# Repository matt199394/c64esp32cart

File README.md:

Inspired on  chat64 cart by Bart Venneker and Theo van den Beld (https://github.com/bvenneker/Chat64), same hardware with some midifications:
- SD card
- 27C512 EEPROM
- add jumpers to select 8k memory inside EEPROM
- add transistor to control EXROM line
- standart or ultiMax mode jumper
  
 About the code:
  The arduino skeck and ACME assembly code are a working progress, there are many bugs to fix, expecialy SD directory code.
  Not all SIDs file are playable, same as PRG file.
  
Feaures:
- Run PRG file
- play SID files and show SID info
- show koala images
- show current time
- show current weather
- show news by using 2x2 charset

  Video to show the cart in action: https://www.youtube.com/watch?v=Q0KYe2STK2w
  
Any help is appreciate,
Have fun!

Matteo

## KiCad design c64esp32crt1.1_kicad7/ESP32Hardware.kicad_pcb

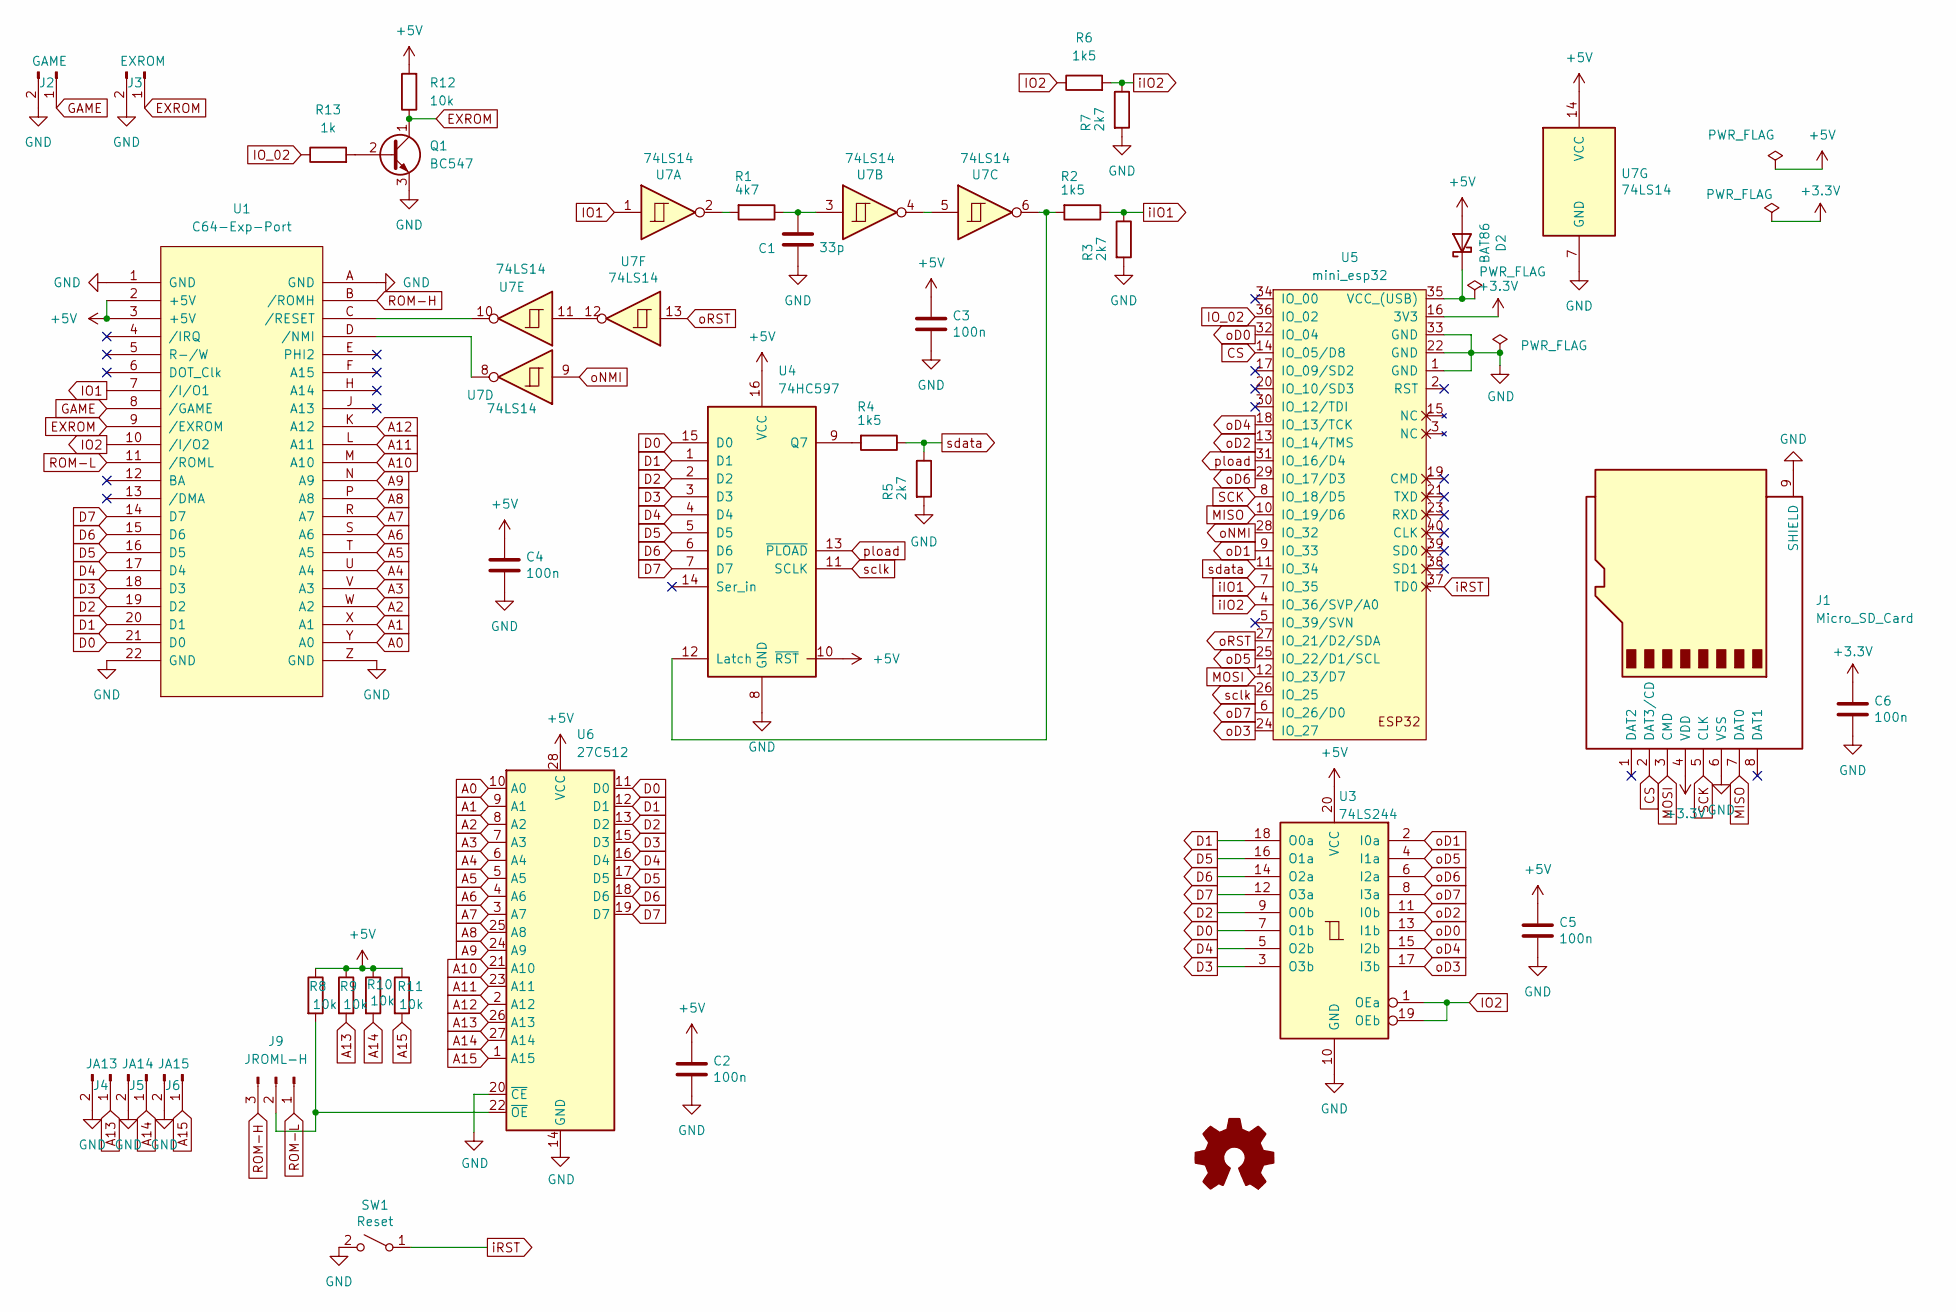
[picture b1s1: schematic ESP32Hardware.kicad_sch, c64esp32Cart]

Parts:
C1: 33p; C_Disc_D3.0mm_W1.6mm_P2.50mm
C2, C3, C4, C5, C6: 100n; C_0805_2012Metric
D2: BAT86; D_DO-34_SOD68_P7.62mm_Horizontal
J1: Micro_SD_Card; J_SD_Card-micro_socket_A
J2: GAME; PinHeader_1x02_P2.54mm_Vertical
J3: EXROM; PinHeader_1x02_P2.54mm_Vertical
J4: JA13; PinHeader_1x02_P2.54mm_Vertical
J5: JA14; PinHeader_1x02_P2.54mm_Vertical
J6: JA15; PinHeader_1x02_P2.54mm_Vertical
J9: JROML-H; PinHeader_1x03_P2.54mm_Vertical
LOGO1: Logo_Open_Hardware_Small; OSHW-Logo2_14.6x12mm_SilkScreen
Q1: BC547; TO-92_Inline
R1: 4k7; R_0805_2012Metric
R2, R4, R6: 1k5; R_0805_2012Metric
R3, R5, R7: 2k7; R_0805_2012Metric
R8, R9, R10, R11, R12: 10k; R_0805_2012Metric
R13: 1k; R_0805_2012Metric
SW1: Reset; SW_Tactile_SKHH_Angled
U1: C64-Exp-Port; C64-Cart-NoSilkS
U3: 74LS244; SOIC-20W_7.5x12.8mm_P1.27mm
U4: 74HC597; SOIC-16W_5.3x10.2mm_P1.27mm
U5: mini_esp32; ESP32_mini
U6: 27C512; DIP-28_W15.24mm
U7: 74LS14; SOIC-14_3.9x8.7mm_P1.27mm

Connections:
+3.3V: C6.1, J1.4 (VDD), U5.16 (3V3)
+5V: C2.1, C3.1, C4.1, C5.1, D2.2 (A), R8.1, R9.1, R10.1, R11.1, R12.2, U1.2 (+5V), U1.3 (+5V), U3.20 (VCC), U4.10 (~RST), U4.16 (VCC), U6.28 (VCC), U7.14 (VCC)
A0: U1.Y (A0), U6.10 (A0)
A1: U1.X (A1), U6.9 (A1)
A2: U1.W (A2), U6.8 (A2)
A3: U1.V (A3), U6.7 (A3)
A4: U1.U (A4), U6.6 (A4)
A5: U1.T (A5), U6.5 (A5)
A6: U1.S (A6), U6.4 (A6)
A7: U1.R (A7), U6.3 (A7)
A8: U1.P (A8), U6.25 (A8)
A9: U1.N (A9), U6.24 (A9)
A10: U1.M (A10), U6.21 (A10)
A11: U1.L (A11), U6.23 (A11)
A12: U1.K (A12), U6.2 (A12)
A13: J4.1, R9.2, U6.26 (A13)
A14: J5.1, R10.2, U6.27 (A14)
A15: J6.1, R11.2, U6.1 (A15)
CS: J1.2 (DAT3/CD), U5.14 (IO_05/D8)
D0: U1.21 (D0), U3.7 (O1b), U4.15 (D0), U6.11 (D0)
D1: U1.20 (D1), U3.18 (O0a), U4.1 (D1), U6.12 (D1)
D2: U1.19 (D2), U3.9 (O0b), U4.2 (D2), U6.13 (D2)
D3: U1.18 (D3), U3.3 (O3b), U4.3 (D3), U6.15 (D3)
D4: U1.17 (D4), U3.5 (O2b), U4.4 (D4), U6.16 (D4)
D5: U1.16 (D5), U3.16 (O1a), U4.5 (D5), U6.17 (D5)
D6: U1.15 (D6), U3.14 (O2a), U4.6 (D6), U6.18 (D6)
D7: U1.14 (D7), U3.12 (O3a), U4.7 (D7), U6.19 (D7)
EXROM: J3.1, Q1.1 (C), R12.1, U1.9 (/EXROM)
GAME: J2.1, U1.8 (/GAME)
GND: C1.2, C2.2, C3.2, C4.2, C5.2, C6.2, J1.6 (VSS), J1.9 (SHIELD), J2.2, J3.2, J4.2, J5.2, J6.2, Q1.3 (E), R3.2, R5.2, R7.2, SW1.2 (B), U1.1 (GND), U1.22 (GND), U1.A (GND), U1.Z (GND), U3.10 (GND), U4.8 (GND), U5.1 (GND), U5.22 (GND), U5.33 (GND), U6.14 (GND), U6.20 (~CE), U7.7 (GND)
IO1: U1.7 (/I/O1), U7.1
IO2: R6.1, U1.10 (/I/O2), U3.1 (OEa), U3.19 (OEb)
IO_02: R13.1, U5.36 (IO_02)
MISO: J1.7 (DAT0), U5.10 (IO_19/D6)
MOSI: J1.3 (CMD), U5.12 (IO_23/D7)
unnamed: C1.1, R1.1, U7.3
unnamed: D2.1 (K), U5.35 (VCC_(USB))
unnamed: J9.2, R8.2, U6.22 (~OE)
unnamed: Q1.2 (B), R13.2
unnamed: R1.2, U7.2
unnamed: U1.D (/NMI), U7.8
unnamed: U1.C (/RESET), U7.10
unnamed: R2.2, U4.12 (Latch), U7.6
unnamed: R4.2, U4.9 (Q7)
unnamed: U7.4, U7.5
unnamed: U7.11, U7.12
ROM-H: J9.3, U1.B (/ROMH)
ROM-L: J9.1, U1.11 (/ROML)
SCK: J1.5 (CLK), U5.8 (IO_18/D5)
iIO1: R2.1, R3.1, U5.7 (IO_35)
iIO2: R6.2, R7.1, U5.4 (IO_36/SVP/A0)
iRST: SW1.1 (A), U5.37 (TD0)
oD0: U3.13 (I1b), U5.32 (IO_04)
oD1: U3.2 (I0a), U5.9 (IO_33)
oD2: U3.11 (I0b), U5.13 (IO_14/TMS)
oD3: U3.17 (I3b), U5.24 (IO_27)
oD4: U3.15 (I2b), U5.18 (IO_13/TCK)
oD5: U3.4 (I1a), U5.25 (IO_22/D1/SCL)
oD6: U3.6 (I2a), U5.29 (IO_17/D3)
oD7: U3.8 (I3a), U5.6 (IO_26/D0)
oNMI: U5.28 (IO_32), U7.9
oRST: U5.27 (IO_21/D2/SDA), U7.13
pload: U4.13 (~PLOAD), U5.31 (IO_16/D4)
sclk: U4.11 (SCLK), U5.26 (IO_25)
sdata: R4.1, R5.1, U5.11 (IO_34)

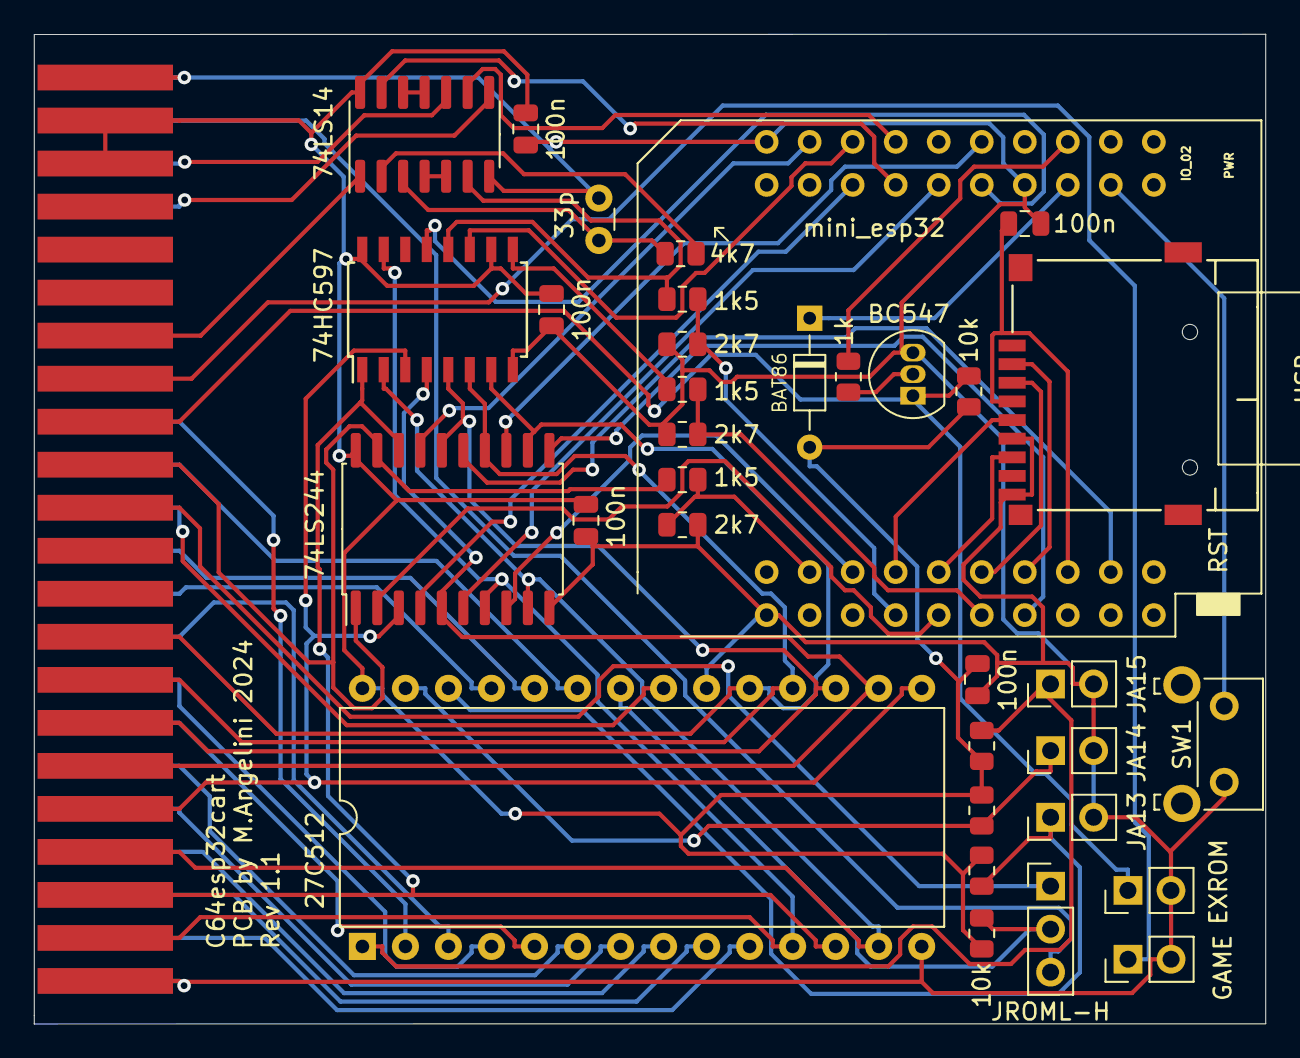
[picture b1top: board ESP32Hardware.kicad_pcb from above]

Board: 2 copper layers, 72.7 x 58.4 mm, 36 parts (0 on the bottom side), 65 nets.

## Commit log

2026-01-07 Update c64esp32Cart.ino
    remove psw
2026-01-07 Update c64esp32Cart.ino
    remove api key
